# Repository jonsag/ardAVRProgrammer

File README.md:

# ardATProgrammer

Some code and a shield for programming ATMega328 and ATtiny85

## Additional Boards Managers URL

Insert these URLs in File -> Preferences -> Settings tab  

>damellis: [https://raw.githubusercontent.com/damellis/attiny/ide-1.6.x-boards-manager/package_damellis_attiny_index.json](https://raw.githubusercontent.com/damellis/attiny/ide-1.6.x-boards-manager/package_damellis_attiny_index.json)  
>leonardomilliani: [http://www.leonardomiliani.com/repository/package_leonardomiliani.com_index.json](http://www.leonardomiliani.com/repository/package_leonardomiliani.com_index.json)  
>carlosefr: [https://raw.githubusercontent.com/carlosefr/atmega/master/package_carlosefr_atmega_index.json](https://raw.githubusercontent.com/carlosefr/atmega/master/package_carlosefr_atmega_index.json)  

Then install boards in Tools -> Board -> Boards manager...  

>attiny  
>ATtiny extra Boards  
>ATmega 168P/328P Boards  
>Barebones ATmega Chips (no bootloader)  

## Burn bootloader, settings

### ATtiny85

Board -> ATtiny Microcontrollers -> ATtiny 25/45/85  
Processor -> ATtiny85  
Clock -> ...  
Programmer -> Arduino as ISP  

### ATtiny2313

Board -> ATtiny MCUs -> ATtiny2313/4313  
Micro -> ATtiny2313 @ ...  
Programmer -> Arduino as ISP

### ATmega328P

Board -> Arduino AVR Boards -> Arduino Duemilanove or or Diecimila  
Processor -> ATmega 328P  
Programmer -> Arduino as AVR  

or  

Board -> Atmega168/328 -> Atmega168/328  
Micro -> ATmega328P @ ... w/Arduino as ISP  

### ATmega328

Board -> ATmega Microcontrollers -> ATmega328/328P  
Processor -> ATmega328  
Clock -> ...  
Programmer -> Arduino as ISP  

## Program AVR, settings

### ATtiny85

Board -> ATtiny Microcontrollers -> ATtiny 25/45/85  
Processor -> ATtiny85  
Clock -> ...  
Programmer -> Arduino as ISP

### ATtiny2313

Board -> ATtiny MCUs -> ATtiny2313/4313  
Micro -> ATtiny2313 @ ...  
Programmer -> Arduino as ISP

### ATmega328P

Board -> Arduino AVR Boards -> Arduino Duemilanove or or Diecimila  
Processor -> ATmega 328P  
Programmer -> Arduino as AVR  

or  

Board -> Atmega168/328 -> Atmega168/328  
Micro -> ATmega328P @ ... w/Arduino as ISP

### ATmega328

Board -> ATmega Microcontrollers -> ATmega328/328P  
Processor -> ATmega328  
Clock -> ...  
Programmer -> Arduino as ISP

## Pin Mapping, Arduino IDE -> AVR

### Arduino code -> ATtiny85 pin number -> Pin name -> Function

0 -> 5 -> PB0 -> (PWM, AIN0)  
1 -> 6 -> PB1 -> (PWM, AIN1)  
2 -> 7 -> PB2 -> (ADC1)  
3 -> 2 -> PB3 -> (ADC3)  
4 -> 3 -> PB4 -> (ADC2)  
5 -> 1 -> PB5 -> (RESET, ADC0)  

### Arduino code -> ATmega328 pin number -> Pin name -> Function

  -> 1 -> PC6 -> (RESET)  
0 -> 2 -> PD0 -> Digital pin 0 (Rx)  
1 -> 3 -> PD1 -> Digital pin 1 (Tx)  
2 -> 4 -> PD2 -> Digital pin 2  
3 -> 5 -> PD3 -> Digital pin 3 (PWM)  
4 -> 6 -> PD4 -> Digital pin 4  
5 -> 11 -> PD5 -> Digital pin 5  
6 -> 12 -> PD6 -> Digital pin 6  
7 -> 13 -> PD7 -> Digital pin 7  
8 -> 14 -> PB0 -> Digital pin 8  
9 -> 15 -> PB1 -> Digital pin 9 (PWM)  
10 -> 16 -> PB2 -> Digital pin 10 (PWM)  
11 -> 17 -> PB3 -> Digital pin 11 (PWM)  
12 -> 18 -> PB4 -> Digital pin 12  
13 -> 19 -> PB5 -> Digital pin 13  
14 -> 23 -> PC0 -> Analog input 0  
15 -> 24 -> PC1 -> Analog input 1  
16 -> 25 -> PC2 -> Analog input 2  
17 -> 26 -> PC3 -> Analog input 3  
18 -> 27 -> PC4 -> Analog input 4  
19 -> 28 -> PC5 -> Analog input 5  

## Atmega_Board_Programmer

### attiny85@16MHz internal

#### Before bootburning

>Signature = 0x1E 0x93 0x0B  
>Processor = ATtiny85  
>Flash memory size = 8192 bytes.  
>LFuse = 0x62  
>HFuse = 0xDF  
>EFuse = 0xFF  
>Lock byte = 0xFF  
>Clock calibration = 0x91  
>No bootloader support.  
>  
>First 256 bytes of program memory:  
>  
>00: 0xFF 0xFF 0xFF 0xFF 0xFF 0xFF 0xFF 0xFF ...  

#### After bootburning

>Signature = 0x1E 0x93 0x0B  
>Processor = ATtiny85  
>Flash memory size = 8192 bytes.  
>LFuse = 0xF1  
>HFuse = 0xDF  
>EFuse = 0xFF  
>Lock byte = 0xFF  
>Clock calibration = 0x86  
>No bootloader support.  
>  
>First 256 bytes of program memory:  
>  
>00: 0xFF 0xFF 0xFF 0xFF 0xFF 0xFF 0xFF 0xFF ...  

#### After programming

>Signature = 0x1E 0x93 0x0B  
>Processor = ATtiny85  
>Flash memory size = 8192 bytes.  
>LFuse = 0xF1  
>HFuse = 0xDF  
>EFuse = 0xFF  
>Lock byte = 0xFF  
>Clock calibration = 0x86  
>No bootloader support.  
>  
>First 256 bytes of program memory:  
>  
>00: 0x23 0xC0 0x32 0xC0 0x31 0xC0 0x30 0xC0 ...  

### ATmega328P as 'Arduino Duemilanove or Diecimila'

#### After bootburning

>Signature = 0x1E 0x95 0x0F  
>Processor = ATmega328P  
>Flash memory size = 32768 bytes.  
>LFuse = 0xFF  
>HFuse = 0xDA  
>EFuse = 0xFD  
>Lock byte = 0xCF  
>Clock calibration = 0xA5  
>Bootloader in use: Yes  
>EEPROM preserved through erase: No  
>Watchdog timer always on: No  
>Bootloader is 2048 bytes starting at 7800  
>  
>Bootloader:  
>  
>7800: 0x0C 0x94 0x34 0x3C 0x0C 0x94 0x51 0x3C ...  
>...  
>MD5 sum of bootloader = 0x0A 0xAC 0xF7 0x16 0xF4 0x3C 0xA2 0xC9 0x27 0x7E 0x08 0xB9 0xD6 0x90 0xBC 0x02  
>Bootloader name: ATmegaBOOT_168_atmega328  
>  
>First 256 bytes of program memory:  
>  
>00: 0xFF 0xFF 0xFF 0xFF 0xFF 0xFF 0xFF 0xFF ...  

### ATmega328 as 'ATmega328/328P' @1Mhz Internal

#### After bootburning

>Signature = 0x1E 0x95 0x14  
>Processor = ATmega328  
>Flash memory size = 32768 bytes.  
>LFuse = 0x62  
>HFuse = 0xDB  
>EFuse = 0xFD  
>Lock byte = 0xFF  
>Clock calibration = 0xA9  
>Bootloader in use: No  
>EEPROM preserved through erase: No  
>Watchdog timer always on: No  
>Bootloader is 1024 bytes starting at 7C00  
>  
>Bootloader:  
>  
>7C00: 0xFF 0xFF 0xFF 0xFF 0xFF 0xFF 0xFF 0xFF ...  
>...  
>MD5 sum of bootloader = 0x69 0x42 0x94 0x9C 0x5B 0x44 0x30 0xAE 0xF6 0x63 0x8B 0x89 0xBF 0xE1 0x73 0x2B  
>Bootloader MD5 sum not known.  
>  
>First 256 bytes of program memory:  
>  
>00: 0xFF 0xFF 0xFF 0xFF 0xFF 0xFF 0xFF 0xFF ...  

#### After programming

>Signature = 0x1E 0x95 0x14  
>Processor = ATmega328  
>Flash memory size = 32768 bytes.  
>LFuse = 0x62  
>HFuse = 0x01  
>EFuse = 0xFD  
>Lock byte = 0xFF  
>Clock calibration = 0xA9  
>Bootloader in use: No  
>EEPROM preserved through erase: No  
>Watchdog timer always on: No  
>Bootloader is 2048 bytes starting at 7800  
>  
>Bootloader:  
>  
>7800: 0xFF 0xFF 0xFF 0xFF 0xFF 0xFF 0xFF ...  
>  
>MD5 sum of bootloader = 0xCB 0xAC 0x33 0x2A 0x4E 0x08 0xAC 0xA7 0xCF 0xFF 0xE0 0xB1 0x42 0xAA 0x0C 0x65  
>Bootloader MD5 sum not known.  
>  
>First 256 bytes of program memory:  
>  
>00: 0x0C 0x94 0x5C 0x00 0x0C 0xCD 0x6E 0x00 ...  
### ATmega328 as 'ATmega328/328P' @8Mhz Internal

#### After bootburning  

>Signature = 0x1E 0x95 0x14  
>Processor = ATmega328  
>Flash memory size = 32768 bytes.  
>LFuse = 0xE2  
>HFuse = 0xDB  
>EFuse = 0xFD  
>Lock byte = 0xFF  
>Clock calibration = 0xA8  
>Bootloader in use: No  
>EEPROM preserved through erase: No  
>Watchdog timer always on: No  
>Bootloader is 2048 bytes starting at 7800  
>  
>Bootloader:  
>  
>7800: 0xFF 0xFF 0xFF 0xFF 0xFF 0xFF 0xFF 0xFF ...  
>...  
>MD5 sum of bootloader = 0xE0 0xDE 0xEB 0xD3 0xC3 0xF5 0x60 0x21 0x2A 0xF1 0x7C 0x68 0xB9 0x34 0x4B 0xAE  
>No bootloader (all 0xFF)  
>  
>First 256 bytes of program memory:  
>  
>00: 0xFF 0xFF 0xFF 0xFF 0xFF 0xFF 0xFF 0xFF ...  

#### After programming

>Signature = 0x1E 0x95 0x14  
>Processor = ATmega328  
>Flash memory size = 32768 bytes.  
>LFuse = 0xE2  
>HFuse = 0xDB  
>EFuse = 0xFD  
>Lock byte = 0xFF  
>Clock calibration = 0xA8  
>Bootloader in use: No  
>EEPROM preserved through erase: No  
>Watchdog timer always on: No  
>Bootloader is 2048 bytes starting at 7800  
>  
>Bootloader:  
>  
>7800: 0xFF 0xFF 0xFF 0xFF 0xFF 0xFF 0xFF ...  
>...  
>MD5 sum of bootloader = 0xE0 0xDE 0xEB 0xD3 0xC3 0xF5 0x60 0x21 0x2A 0xF1 0x7C 0x68 0xB9 0x34 0x4B 0xAE  
>No bootloader (all 0xFF)  
>  
>First 256 bytes of program memory:  
>  
>00: 0x0C 0x94 0x5C 0x00 0x0C 0x94 0x6E 0x00 ...  

## Resources

[Breadboard @gammon.com](http://www.gammon.com.au/breadboard) (excellent!)  
[nickgammon arduino sketches @github](https://github.com/nickgammon/arduino_sketches)  
[Alternative Atmega bootloader programmer @gammon.com](http://www.gammon.com.au/forum/?id=11635)  
[Phenoptix @github](https://github.com/phenoptix/AVRISP)

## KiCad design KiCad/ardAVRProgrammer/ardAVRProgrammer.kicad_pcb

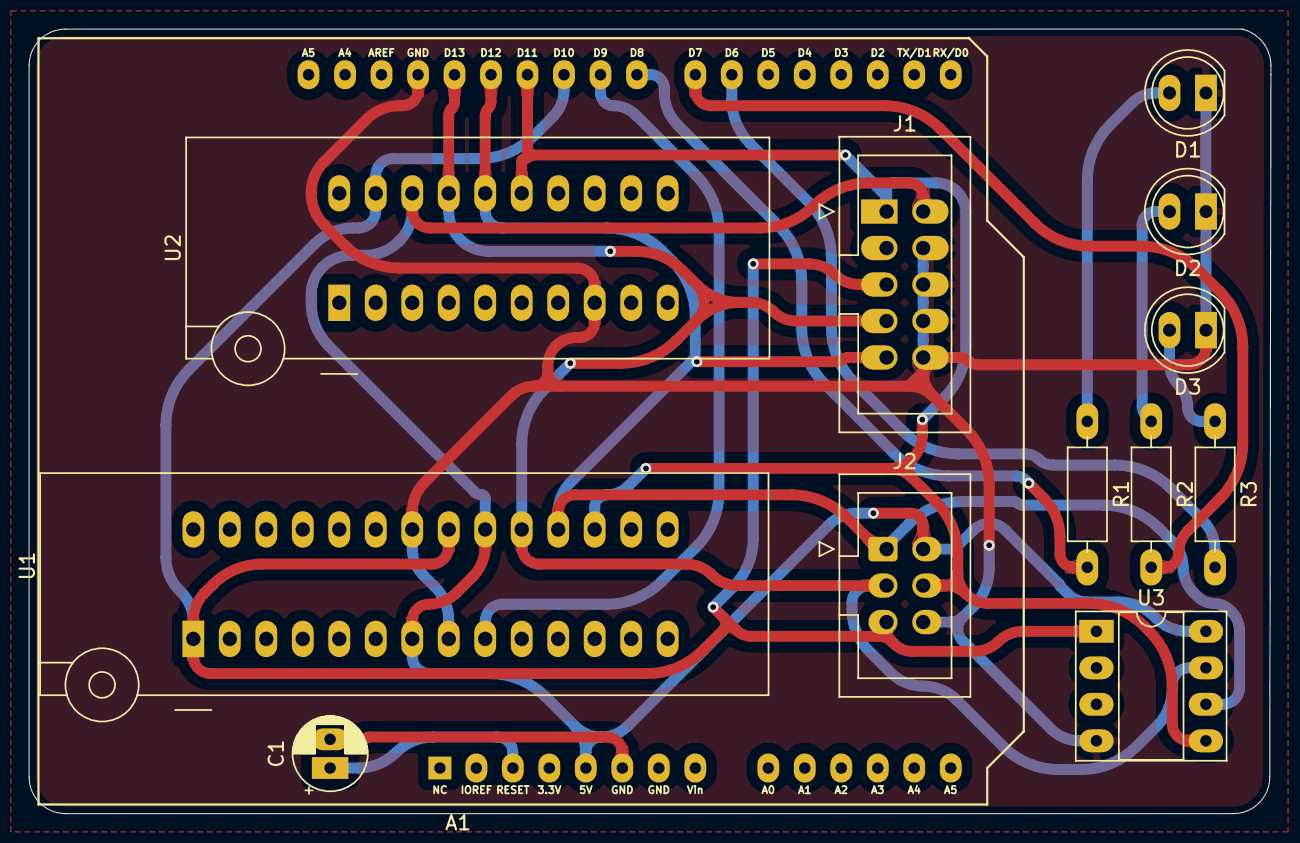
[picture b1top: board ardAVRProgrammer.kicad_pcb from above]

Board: 2 copper layers, 86.4 x 54.6 mm, 13 parts (0 on the bottom side), 15 nets.

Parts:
A1: Arduino_UNO_R3; Arduino_UNO_R3_shield_large
C1: 10u; CP_Radial_D5.0mm_P2.00mm_larger
D1, D2, D3: LED; LED_D5.0mm_larger_pads
J1: 2x5_ISP_header; IDC-Header_2x05_P2.54mm_Vertical_large
J2: 2x3_ISP_header; IDC-Header_2x03_P2.54mm_Vertical large
R1, R2, R3: 330R; R_Axial_DIN0207_L6.3mm_D2.5mm_P10.16mm_Horizontal_larger_pa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
U1: ATmega328P-PU; ZIF_DIP_Socket-28_W6.9_W7.62_W7.62_W12.7_W13.5_large
U2: ATtiny2313-20M; ZIF_DIP_Socket-20_W4.3_W5.08_W7.62_W10.16_W10.9_3M_220-3342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
U3: ATtiny85-20P; DIP-8_W7.62mm_Socket_w_dip_packet_LongPads

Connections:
+5V: A1.5 (+5V), J1.2 (VCC), J2.2 (VCC), U1.7 (VCC), U1.20 (AVCC), U2.18 (VCC), U3.8 (VCC)
GND: A1.29 (GND), D1.1 (K), D2.1 (K), D3.1 (K), J1.4 (GND), J1.6 (GND), J1.8 (GND), J1.10 (GND), J2.6 (GND), U1.8 (GND), U1.22 (GND), U2.8 (GND), U3.4 (GND)
unnamed: A1.3 (~RESET), C1.1
unnamed: A1.6 (GND), C1.2
unnamed: A1.21 (D6), R3.2
unnamed: A1.22 (D7), R2.2
unnamed: A1.23 (D8), R1.2
unnamed: A1.24 (D9), U1.9 (XTAL1/PB6)
unnamed: A1.25 (D10), J1.5 (RST), J2.5 (RST), U1.1 (~RESET/PC6), U1.21 (AREF), U2.19 (PA2/~RESET), U3.1 (~RESET/PB5)
unnamed: A1.26 (D11), J1.1 (MOSI), J2.4 (MOSI), U1.17 (PB3), U2.15 (PB5), U3.5 (AREF/PB0)
unnamed: A1.27 (D12), J1.9 (MISO), J2.1 (MISO), U1.18 (PB4), U2.16 (PB6), U3.6 (PB1)
unnamed: A1.28 (D13), J1.7 (SCK), J2.3 (SCK), U1.19 (PB5), U2.17 (PB7), U3.7 (PB2)
unnamed: D1.2 (A), R1.1
unnamed: D2.2 (A), R2.1
unnamed: D3.2 (A), R3.1

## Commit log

2021-01-28 sketch
2021-01-28 OpenSCAD
2021-01-28 scad
2021-01-29 deleted unnecessary files
2021-01-29 new schematics
2021-01-29 schematics and scad
2021-01-30 README
2021-01-30 ATmega Board Detector
2021-01-30 enclosure
2021-01-30 deleted .gitignore
2021-01-31 Board detector
2022-05-13 kicad6
2022-05-17 new PCB layout
2022-06-03 new kicad
2022-09-09 kicad
2023-02-21 kicad7
2025-01-26 new kicad version
